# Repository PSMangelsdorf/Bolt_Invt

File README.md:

# Bolt_Invt
Open Source drop in logic board for Chevrolet Bolt inverter, based on the collective work of the Open Inverter Project, and especially that of Damien Maguire.

October 10, 2026 - Establishing repo for logic board development.  External pinout established from GM service information.  Internal pinout between logic and gate boards established via probing and tracing.

October 11, 2026 - Initial design completed by Claude - WARNING: This design is completely untested at this point.  ADDITIONAL WARNING: This design does not support the OEM Bolt drive motor/transmission at this time.  It does not drive the pump or read the IMS position.  It has not been configured with the Bolt resolver or temp sensors.

October 31, 2026 - A few updates made to the 5V regulation by Claude, also used Claude to produce gerbers and BOM.  First prototypes have been ordered.

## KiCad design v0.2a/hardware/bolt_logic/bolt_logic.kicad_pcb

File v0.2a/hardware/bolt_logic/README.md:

# bolt_logic — KiCad project

Replacement logic board for the Chevrolet Bolt EV traction inverter.

## Current state (v0.2a — redesign after the forum review)

- **Schematic v0.2a:** 7 hierarchical sheets, 245 parts, 162 nets, drawn as wired sheets in
  signal-flow order.
  - PDF: `../../docs/bolt_logic_schematic.pdf`
  - Design rationale: `../../docs/03-schematic-design.md`
  - What changed and why: `../../docs/06-forum-review.md`
- **PCB v0.2a:** 4 layers (signal / GND / power / signal), placed and routed. Prototype for
  review; see `../../docs/04-layout.md`.

## Regenerating

Everything is generated by scripts; edit the tables, not the outputs. You need KiCad 7+
(`pcbnew` Python module and `kicad-cli`). Routing also needs Java 21, `xvfb-run`,
FreeRouting 1.9 (`FREEROUTING_JAR`) and `shapely`.

```
python3 tools/gen_sch.py      # schematic sheets from tools/sch_design.py + sch_layout.py, netlist verified
python3 tools/gen_mech.py     # outline, holes, CN1/CN2 (asserts every pad position)
python3 tools/gen_layout.py   # netlist -> footprints, pad cross-check, placement
python3 tools/gen_route.py    # planes, buck / crystal / contactor copper, plane fan-out, FreeRouting, pours, DRC
python3 tools/gen_fab.py      # fab/: Gerbers + drill zip, JLCPCB BOM + CPL, full BOM, fab notes
```

`gen_route.py` takes about 10–15 minutes, most of it FreeRouting. Its working files go to
`route_work/` (not committed):
- `--import-only` re-imports the last routing run.
- `--stage2-only` keeps stage 1 and redoes only stage 2.

## Files

- `bolt_logic.kicad_pcb`: generated; don't hand-edit the mechanical items. Hand-tuning of
  the routing (see the review list) is expected later. Once that starts, stop re-running
  `gen_route.py`, because it would overwrite the hand edits.
- `tools/gen_mech.py`: single source of truth for mechanical dimensions.
- `tools/sch_design.py`: the schematic design table (every part, every pin → net).
- `tools/sch_layout.py`: where each symbol is drawn on its sheet, label directions, section notes.
- `tools/gen_layout.py`: placement regions (`GROUPS`), anchors, decoupling pairs (`NEAR`), the 10 mm CN1/CN2 clearance and the height check.
- `tools/gen_route.py`: net classes, In2 power-plane islands, routing flow, GND stitching, chassis ring.
- `tools/buck_block.py`: the hand-designed 5 V buck block (placement and copper).
- `tools/jlc_parts.py`, `tools/gen_fab.py`: proposed LCSC part per BOM line, and the fab package.
- `tools/gen_cn1_compare.py`: writes `../../docs/cn1_oem_vs_new.pdf`, the CN1 OEM-vs-new pin table.
  Re-run it after changing CN1 assignments in `sch_design.py`.
- `Bolt.pretty/`, `Bolt.kicad_sym`: project footprint and symbol libraries.

Coordinate frame and measurement provenance: `../../docs/02-mechanical.md`.
The project is saved in KiCad 7 format. It opens in KiCad 8/9, which will offer to upgrade
the file.

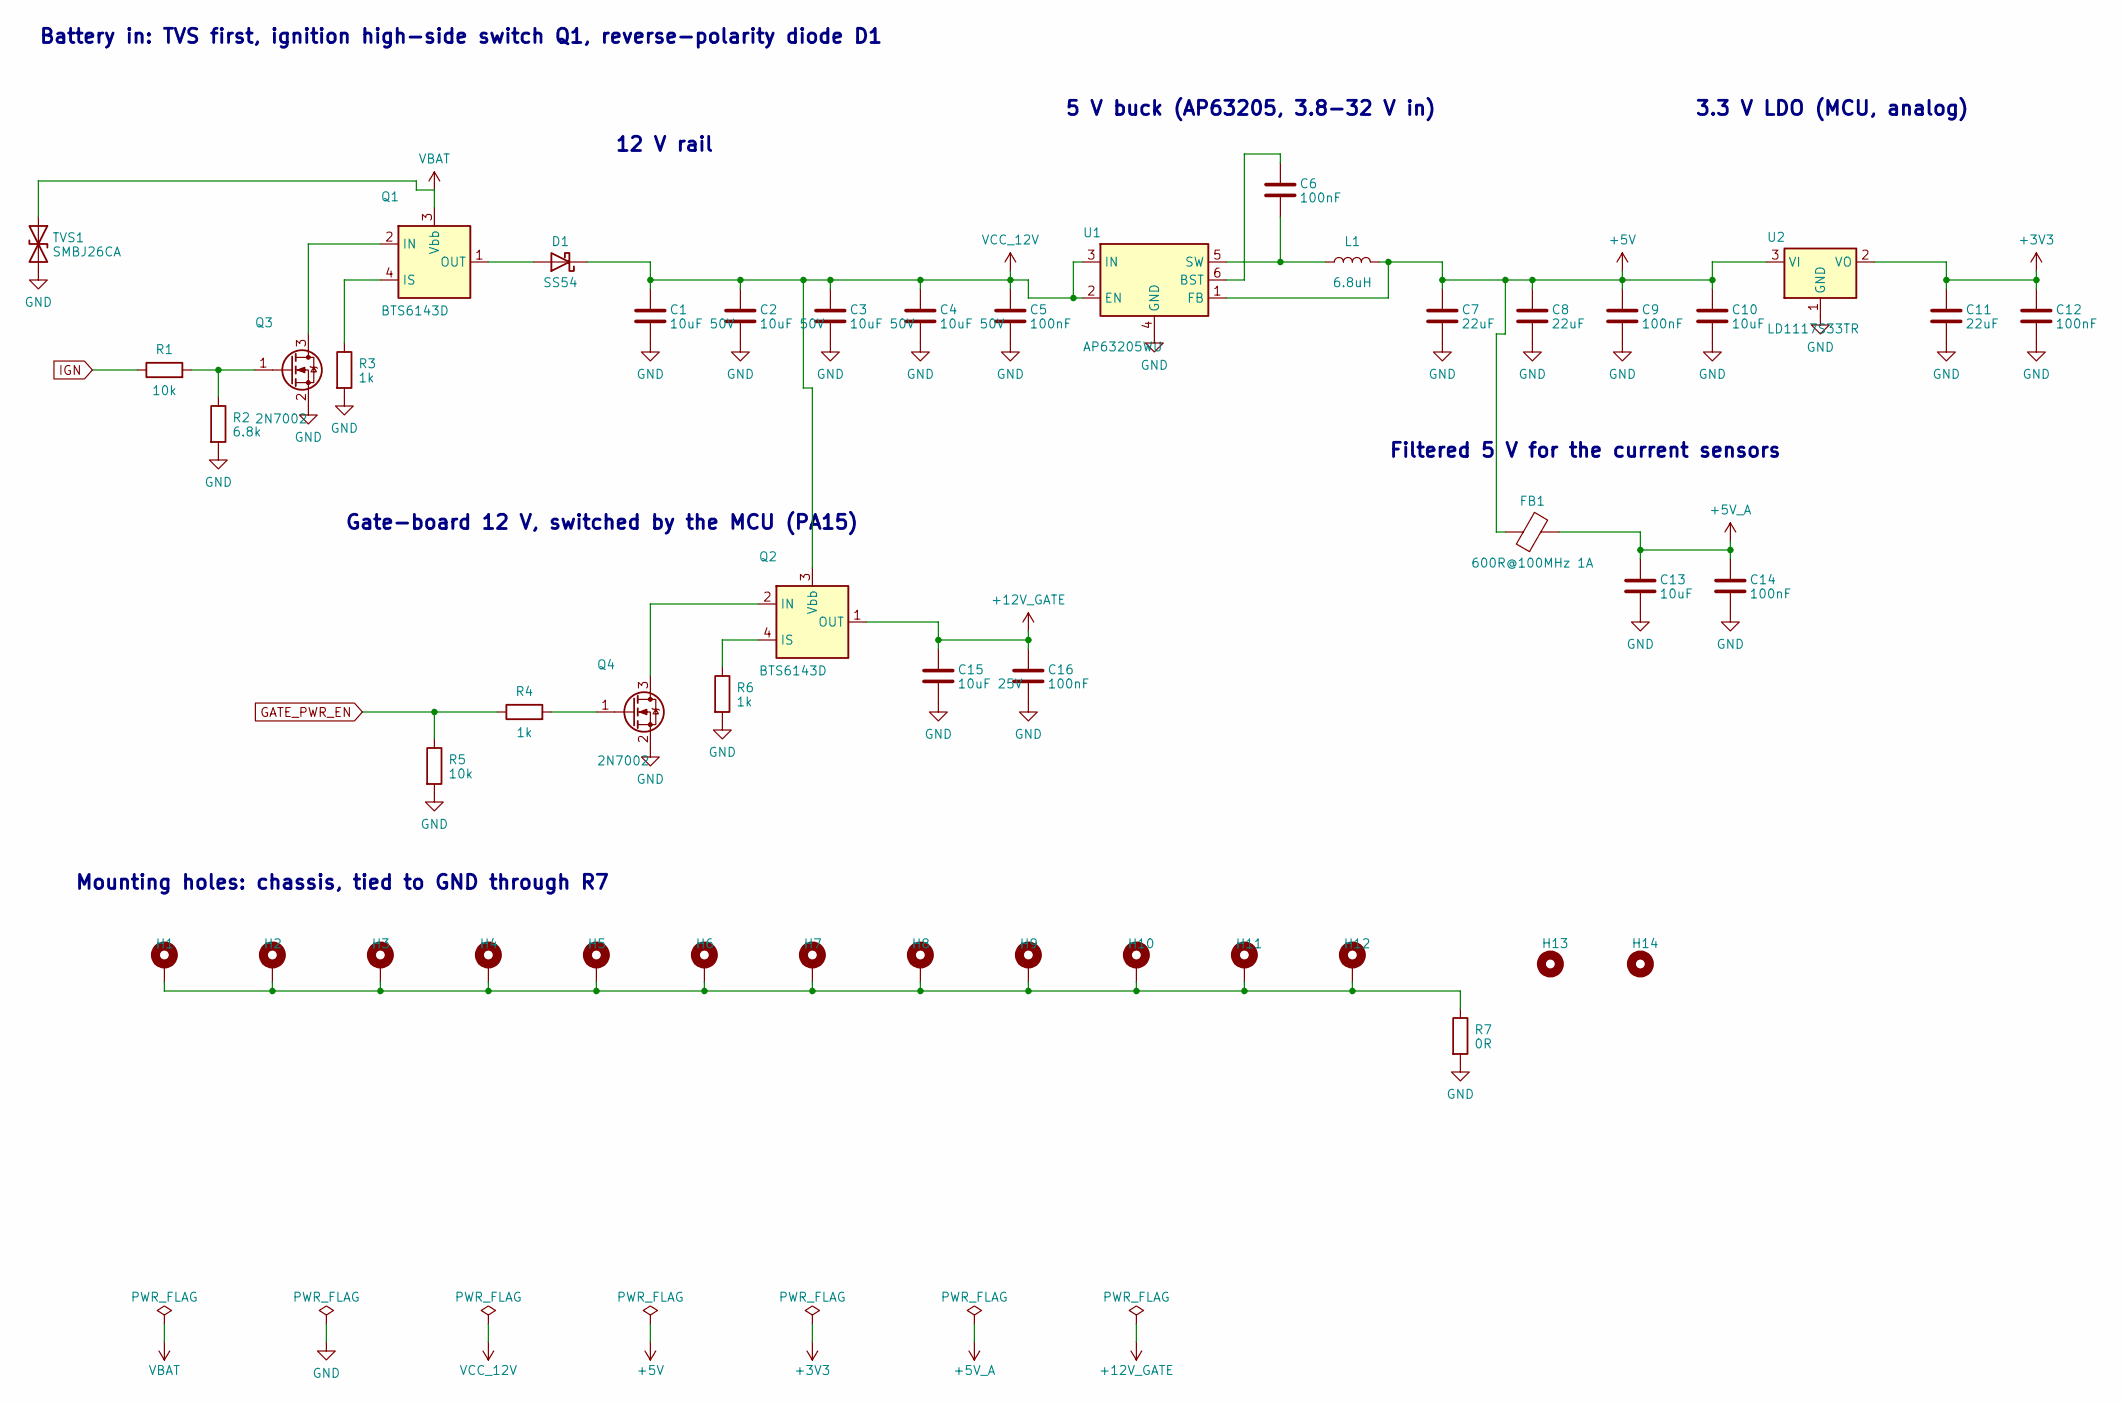
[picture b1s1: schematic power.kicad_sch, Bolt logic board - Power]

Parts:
C1, C2, C3, C4: 10uF 50V; C_1206_3216Metric
C5, C6, C9, C12, C14, C16: 100nF; C_0805_2012Metric
C7, C8, C11: 22uF; C_1206_3216Metric
C10, C13: 10uF; C_1206_3216Metric
C15: 10uF 25V; C_1206_3216Metric
D1: SS54; D_SMA
FB1: 600R@100MHz 1A; L_0805_2012Metric
H1, H2, H3, H4, H5, H6, H7, H8, H9, H10, H11, H12: MountingHole_4mm; MountingHole_4.0mm_Pad6.5
H13, H14: NPTH_4.5mm
L1: 6.8uH; L_Bourns_SRN6045TA
Q1, Q2: BTS6143D; TO-252-4
Q3, Q4: 2N7002; SOT-23
R1, R5: 10k; R_0805_2012Metric
R2: 6.8k; R_0805_2012Metric
R3, R4, R6: 1k; R_0805_2012Metric
R7: 0R; R_1206_3216Metric
TVS1: SMBJ26CA; D_SMB
U1: AP63205WU; TSOT-23-6
U2: LD1117S33TR; SOT-223-3_TabPin2

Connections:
+3V3: C11.1, C12.1, U2.2 (VO); also elsewhere on the board
+5V: C7.1, C8.1, C9.1, C10.1, FB1.1, L1.2, U1.1 (FB), U2.3 (VI); also elsewhere on the board
+5V_A: C13.1, C14.1, FB1.2; also elsewhere on the board
+12V_GATE: C15.1, C16.1, Q2.1 (OUT), Q2.5 (OUT); also elsewhere on the board
BST_5V: C6.1, U1.6 (BST)
CHASSIS: H1.1, H2.1, H3.1, H4.1, H5.1, H6.1, H7.1, H8.1, H9.1, H10.1, H11.1, H12.1, R7.1
GATE_PWR_EN: R4.1, R5.1; also elsewhere on the board
GND: C1.2, C2.2, C3.2, C4.2, C5.2, C7.2, C8.2, C9.2, C10.2, C11.2, C12.2, C13.2, C14.2, C15.2, C16.2, Q3.2 (S), Q4.2 (S), R2.2, R3.2, R5.2, R6.2, R7.2, TVS1.2 (A2), U1.4 (GND), U2.1 (GND); also elsewhere on the board
IGN: R1.1; also elsewhere on the board
Q1_G: Q3.1 (G), R1.2, R2.1
Q1_IN: Q1.2 (IN), Q3.3 (D)
Q1_IS: Q1.4 (IS), R3.1
Q2_G: Q4.1 (G), R4.2
Q2_IN: Q2.2 (IN), Q4.3 (D)
Q2_IS: Q2.4 (IS), R6.1
SW_5V: C6.2, L1.1, U1.5 (SW)
VBAT: Q1.3 (Vbb), TVS1.1 (A1); also elsewhere on the board
VBAT_SW: D1.2 (A), Q1.1 (OUT), Q1.5 (OUT)
VCC_12V: C1.1, C2.1, C3.1, C4.1, C5.1, D1.1 (K), Q2.3 (Vbb), U1.2 (EN), U1.3 (IN); also elsewhere on the board

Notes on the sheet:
Battery in: TVS first, ignition high-side switch Q1, reverse-polarity diode D1
12 V rail
5 V buck (AP63205, 3.8-32 V in)
3.3 V LDO (MCU, analog)
Gate-board 12 V, switched by the MCU (PA15)
Filtered 5 V for the current sensors
Mounting holes: chassis, tied to GND through R7

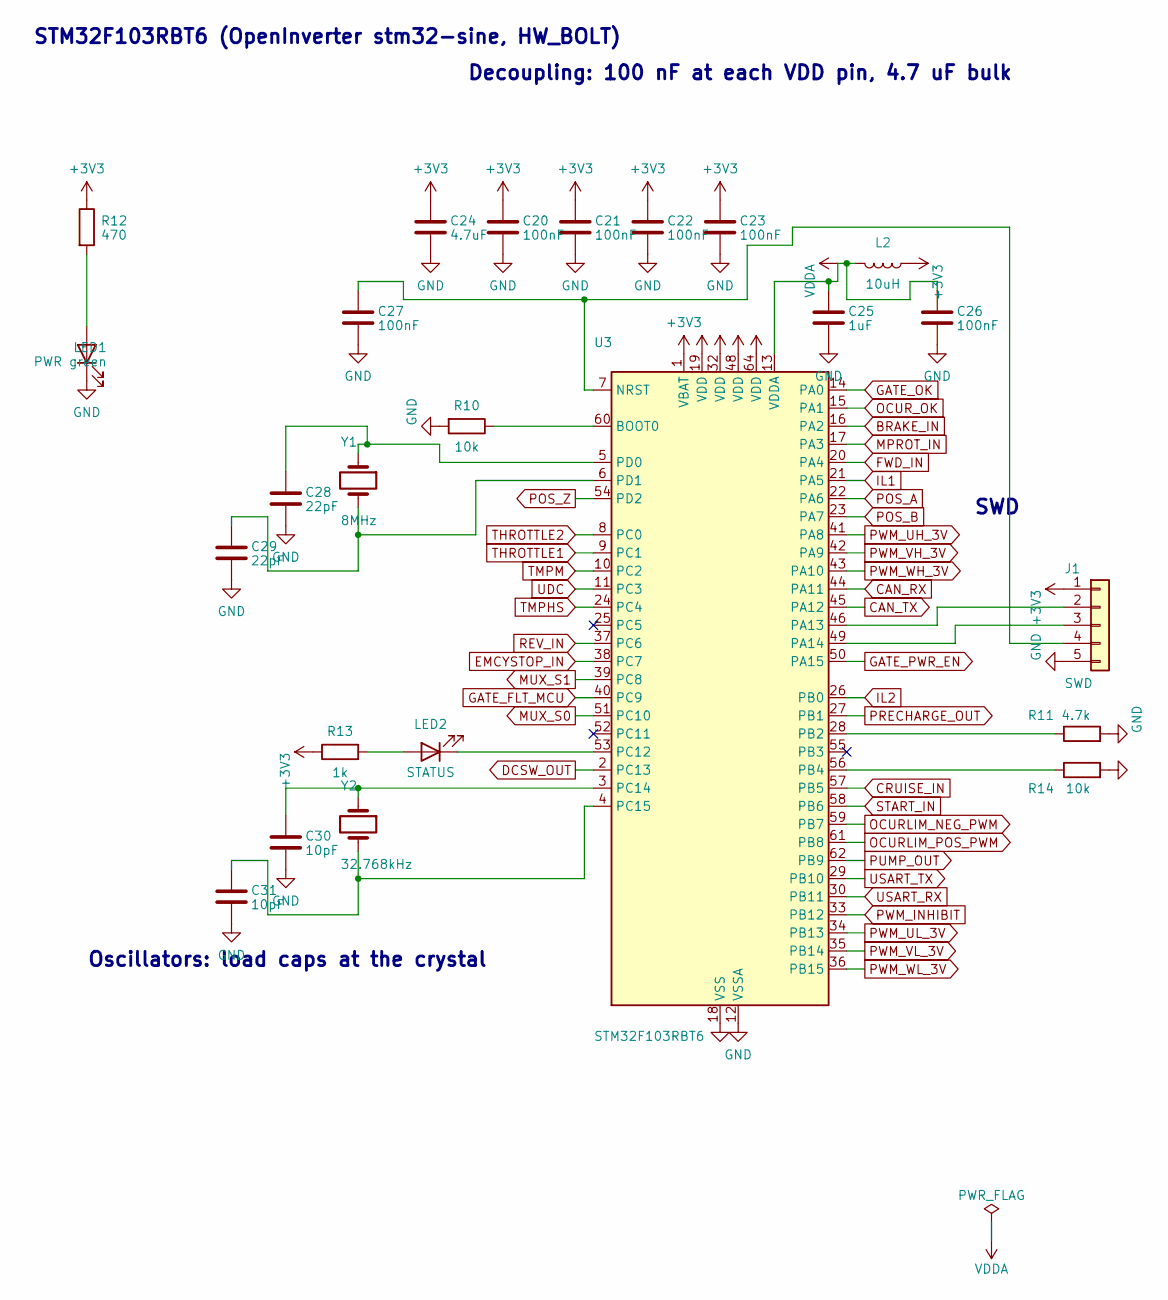
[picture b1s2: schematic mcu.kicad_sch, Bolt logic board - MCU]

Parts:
C20, C21, C22, C23, C26, C27: 100nF; C_0805_2012Metric
C24: 4.7uF; C_0805_2012Metric
C25: 1uF; C_0805_2012Metric
C28, C29: 22pF; C_0805_2012Metric
C30, C31: 10pF; C_0805_2012Metric
J1: SWD; PinHeader_1x05_P2.54mm_Vertical
L2: 10uH; L_0805_2012Metric
LED1: PWR green; LED_0805_2012Metric
LED2: STATUS; LED_0805_2012Metric
R10, R14: 10k; R_0805_2012Metric
R11: 4.7k; R_0805_2012Metric
R12: 470; R_0805_2012Metric
R13: 1k; R_0805_2012Metric
U3: STM32F103RBT6; LQFP-64_10x10mm_P0.5mm
Y1: 8MHz; Crystal_SMD_5032-2Pin_5.0x3.2mm
Y2: 32.768kHz; Crystal_SMD_3215-2Pin_3.2x1.5mm

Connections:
+3V3: C20.1, C21.1, C22.1, C23.1, C24.1, J1.1, L2.1, R12.1, R13.1, U3.1 (VBAT), U3.19 (VDD), U3.32 (VDD), U3.48 (VDD), U3.64 (VDD); also elsewhere on the board
BOARD_ID: R14.1, U3.56 (PB4)
BOOT0: R10.1, U3.60 (BOOT0)
BOOT1: R11.1, U3.28 (PB2)
BRAKE_IN: U3.16 (PA2); also elsewhere on the board
CAN_RX: U3.44 (PA11); also elsewhere on the board
CAN_TX: U3.45 (PA12); also elsewhere on the board
CRUISE_IN: U3.57 (PB5); also elsewhere on the board
DCSW_OUT: U3.2 (PC13); also elsewhere on the board
EMCYSTOP_IN: U3.38 (PC7); also elsewhere on the board
FWD_IN: U3.20 (PA4); also elsewhere on the board
GATE_FLT_MCU: U3.40 (PC9); also elsewhere on the board
GATE_OK: U3.14 (PA0); also elsewhere on the board
GATE_PWR_EN: U3.50 (PA15); also elsewhere on the board
GND: C20.2, C21.2, C22.2, C23.2, C24.2, C25.2, C26.2, C27.2, C28.2, C29.2, C30.2, C31.2, J1.5, LED1.1 (K), R10.2, R11.2, R14.2, U3.12 (VSSA), U3.18 (VSS), U3.31 (VSS), U3.47 (VSS), U3.63 (VSS); also elsewhere on the board
IL1: U3.21 (PA5); also elsewhere on the board
IL2: U3.26 (PB0); also elsewhere on the board
LED1_A: LED1.2 (A), R12.2
LED2_A: LED2.2 (A), R13.2
LED_OUT: LED2.1 (K), U3.53 (PC12)
MPROT_IN: U3.17 (PA3); also elsewhere on the board
MUX_S0: U3.51 (PC10); also elsewhere on the board
MUX_S1: U3.39 (PC8); also elsewhere on the board
NRST: C27.1, J1.4, U3.7 (NRST)
OCURLIM_NEG_PWM: U3.59 (PB7); also elsewhere on the board
OCURLIM_POS_PWM: U3.61 (PB8); also elsewhere on the board
OCUR_OK: U3.15 (PA1); also elsewhere on the board
OSC32_IN: C30.1, U3.3 (PC14), Y2.1
OSC32_OUT: C31.1, U3.4 (PC15), Y2.2
OSC_IN: C28.1, U3.5 (PD0), Y1.1
OSC_OUT: C29.1, U3.6 (PD1), Y1.2
POS_A: U3.22 (PA6); also elsewhere on the board
POS_B: U3.23 (PA7); also elsewhere on the board
POS_Z: U3.54 (PD2); also elsewhere on the board
PRECHARGE_OUT: U3.27 (PB1); also elsewhere on the board
PUMP_OUT: U3.62 (PB9); also elsewhere on the board
PWM_INHIBIT: U3.33 (PB12); also elsewhere on the board
PWM_UH_3V: U3.41 (PA8); also elsewhere on the board
PWM_UL_3V: U3.34 (PB13); also elsewhere on the board
PWM_VH_3V: U3.42 (PA9); also elsewhere on the board
PWM_VL_3V: U3.35 (PB14); also elsewhere on the board
PWM_WH_3V: U3.43 (PA10); also elsewhere on the board
PWM_WL_3V: U3.36 (PB15); also elsewhere on the board
REV_IN: U3.37 (PC6); also elsewhere on the board
START_IN: U3.58 (PB6); also elsewhere on the board
SWCLK: J1.3, U3.49 (PA14)
SWDIO: J1.2, U3.46 (PA13)
THROTTLE1: U3.9 (PC1); also elsewhere on the board
THROTTLE2: U3.8 (PC0); also elsewhere on the board
TMPHS: U3.24 (PC4); also elsewhere on the board
TMPM: U3.10 (PC2); also elsewhere on the board
UDC: U3.11 (PC3); also elsewhere on the board
USART_RX: U3.30 (PB11); also elsewhere on the board
USART_TX: U3.29 (PB10); also elsewhere on the board
VDDA: C25.1, C26.1, L2.2, U3.13 (VDDA)

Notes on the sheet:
STM32F103RBT6 (OpenInverter stm32-sine, HW_BOLT)
Decoupling: 100 nF at each VDD pin, 4.7 uF bulk
Oscillators: load caps at the crystal
SWD

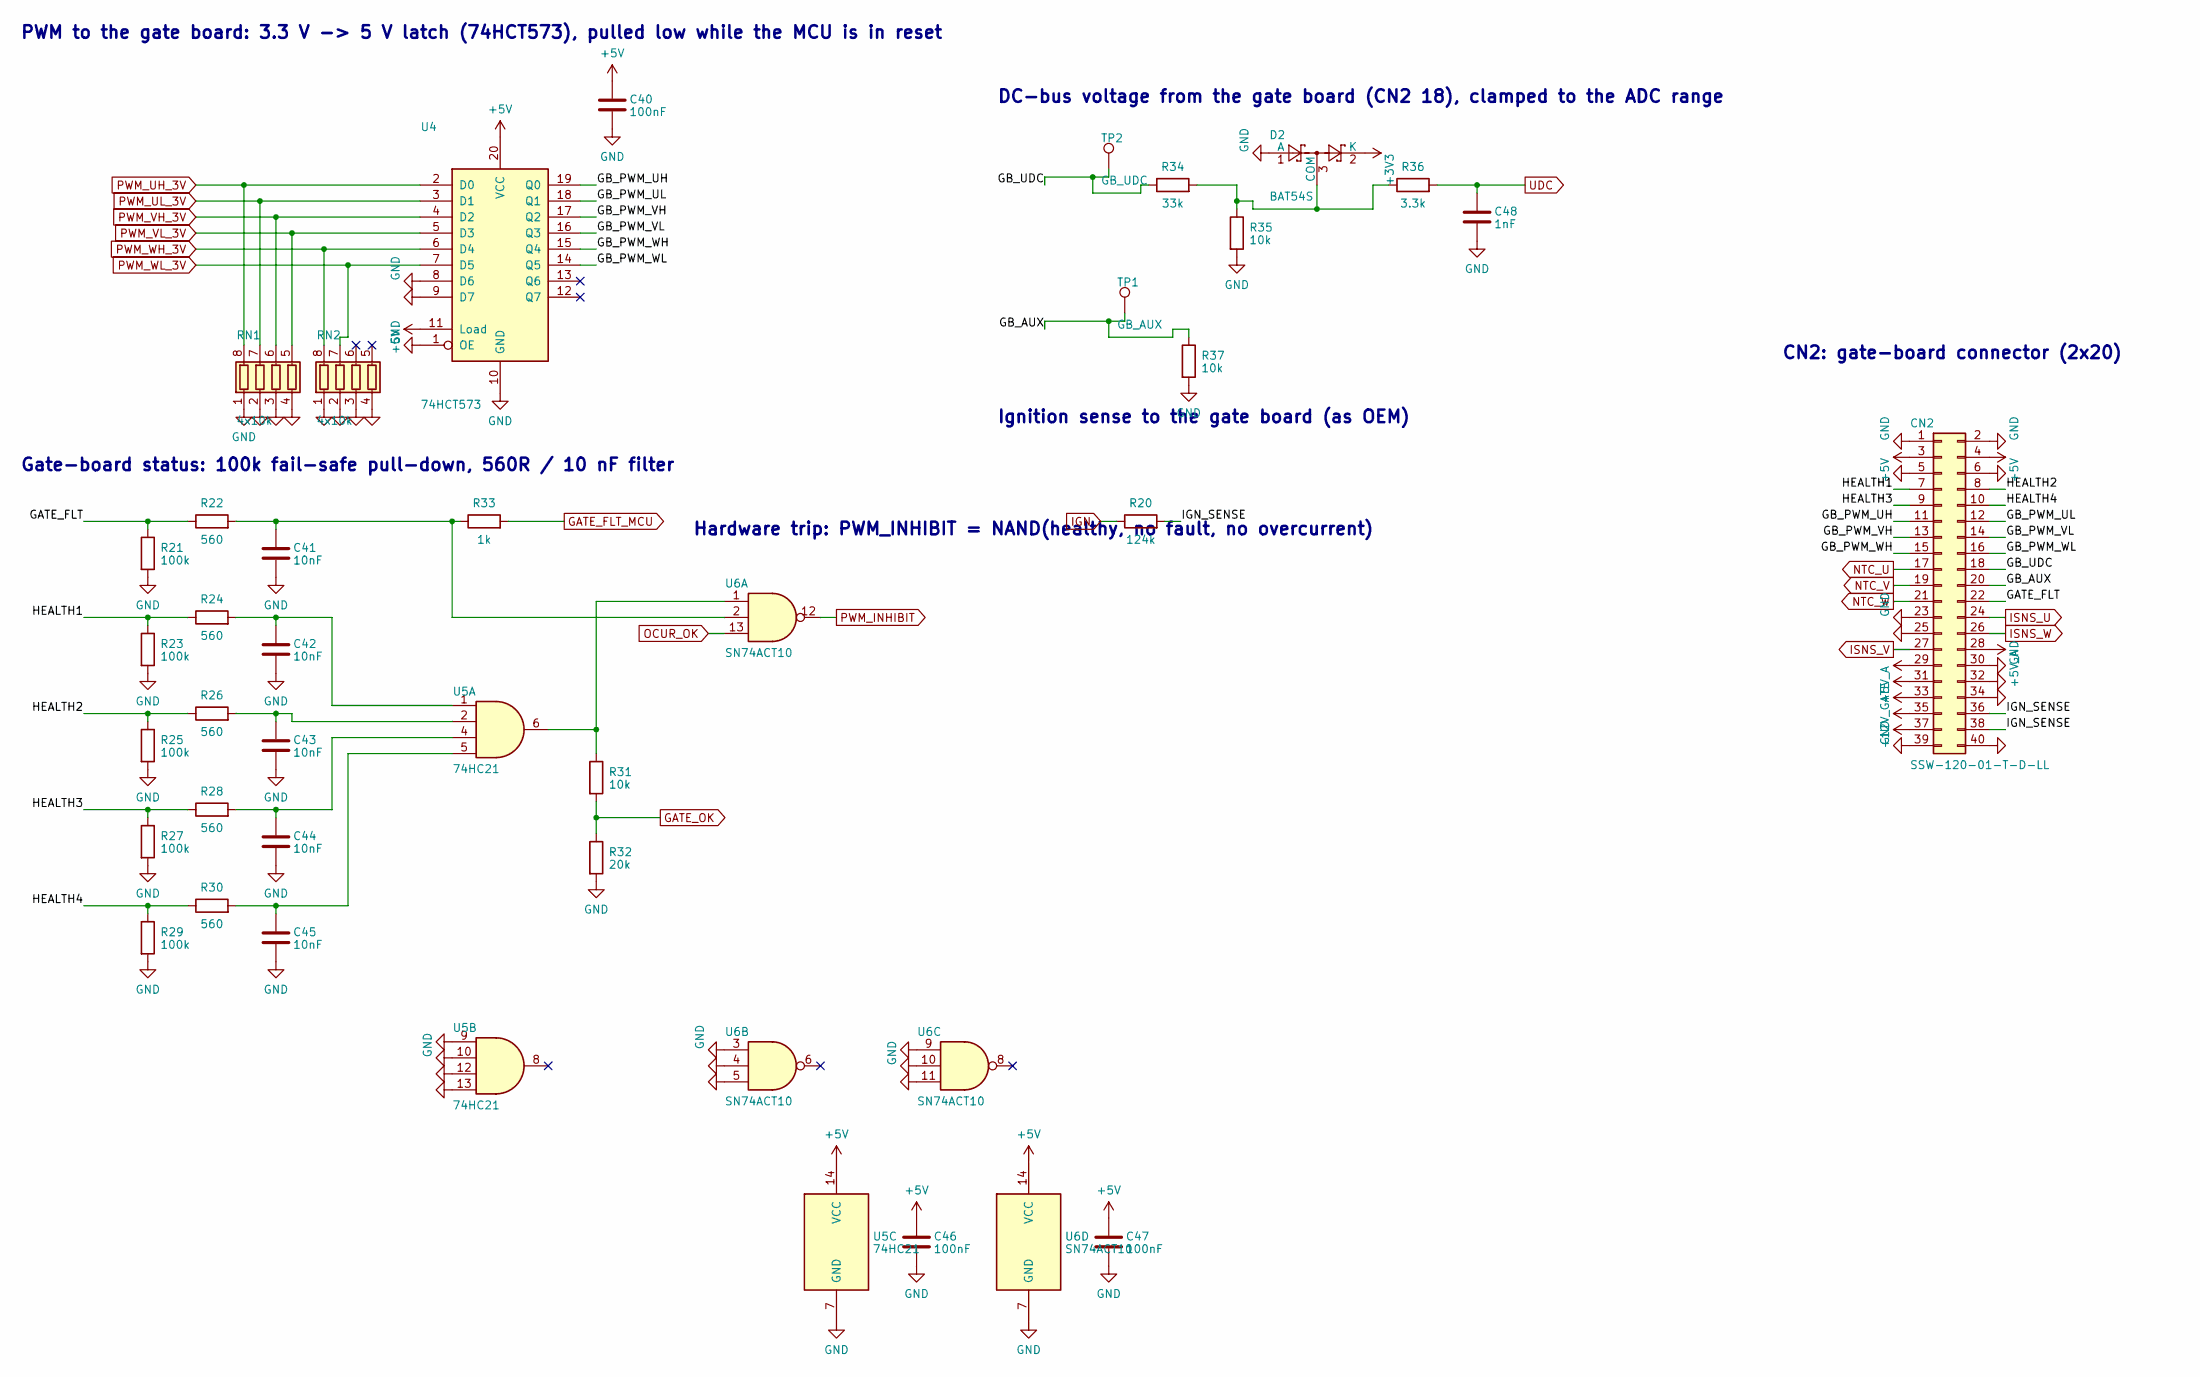
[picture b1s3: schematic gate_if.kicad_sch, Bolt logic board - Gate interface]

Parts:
C40, C46, C47: 100nF; C_0805_2012Metric
C41, C42, C43, C44, C45: 10nF; C_0805_2012Metric
C48: 1nF; C_0805_2012Metric
CN2: SSW-120-01-T-D-LL; CN2_2x20_P2.54_Receptacle_Back
D2: BAT54S; SOT-23
R20: 124k; R_0805_2012Metric
R21, R23, R25, R27, R29: 100k; R_0805_2012Metric
R22, R24, R26, R28, R30: 560; R_0805_2012Metric
R31, R35, R37: 10k; R_0805_2012Metric
R32: 20k; R_0805_2012Metric
R33: 1k; R_0805_2012Metric
R34: 33k; R_0805_2012Metric
R36: 3.3k; R_0805_2012Metric
RN1, RN2: 4x10k; R_Array_Convex_4x0603
TP1: GB_AUX; TestPoint_Pad_D1.5mm
TP2: GB_UDC; TestPoint_Pad_D1.5mm
U4: 74HCT573; SOIC-20W_7.5x12.8mm_P1.27mm
U5: 74HC21; SOIC-14_3.9x8.7mm_P1.27mm
U6: SN74ACT10; SOIC-14_3.9x8.7mm_P1.27mm

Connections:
+3V3: D2.2 (K); also elsewhere on the board
+5V: C40.1, C46.1, C47.1, CN2.3, CN2.4, U4.11 (Load), U4.20 (VCC), U5.14 (VCC), U6.14 (VCC); also elsewhere on the board
+5V_A: CN2.28, CN2.29; also elsewhere on the board
+12V_GATE: CN2.31, CN2.33, CN2.35, CN2.37; also elsewhere on the board
GATE_FLT: CN2.22, R21.1, R22.1
GATE_FLT_F: C41.1, R22.2, R33.1, U6.2
GATE_FLT_MCU: R33.2; also elsewhere on the board
GATE_OK: R31.2, R32.1; also elsewhere on the board
GATE_OK_5V: R31.1, U5.6, U6.1
GB_AUX: CN2.20, R37.1, TP1.1
GB_PWM_UH: CN2.11, U4.19 (Q0)
GB_PWM_UL: CN2.12, U4.18 (Q1)
GB_PWM_VH: CN2.13, U4.17 (Q2)
GB_PWM_VL: CN2.14, U4.16 (Q3)
GB_PWM_WH: CN2.15, U4.15 (Q4)
GB_PWM_WL: CN2.16, U4.14 (Q5)
GB_UDC: CN2.18, R34.1, TP2.1
GND: C40.2, C41.2, C42.2, C43.2, C44.2, C45.2, C46.2, C47.2, C48.2, CN2.1, CN2.2, CN2.5, CN2.6, CN2.23, CN2.25, CN2.30, CN2.32, CN2.34, CN2.39, CN2.40, D2.1 (A), R21.2, R23.2, R25.2, R27.2, R29.2, R32.2, R35.2, R37.2, RN1.1 (R1.1), RN1.2 (R2.1), RN1.3 (R3.1), RN1.4 (R4.1), RN2.1 (R1.1), RN2.2 (R2.1), RN2.3 (R3.1), RN2.4 (R4.1), U4.1 (OE), U4.8 (D6), U4.9 (D7), U4.10 (GND), U5.7 (GND), U5.9, U5.10, U5.12, U5.13, U6.3, U6.4, U6.5, U6.7 (GND), U6.9, U6.10, U6.11; also elsewhere on the board
HEALTH1: CN2.7, R23.1, R24.1
HEALTH1_F: C42.1, R24.2, U5.1
HEALTH2: CN2.8, R25.1, R26.1
HEALTH2_F: C43.1, R26.2, U5.2
HEALTH3: CN2.9, R27.1, R28.1
HEALTH3_F: C44.1, R28.2, U5.4
HEALTH4: CN2.10, R29.1, R30.1
HEALTH4_F: C45.1, R30.2, U5.5
IGN: R20.1; also elsewhere on the board
IGN_SENSE: CN2.36, CN2.38, R20.2
ISNS_U: CN2.24; also elsewhere on the board
ISNS_V: CN2.27; also elsewhere on the board
ISNS_W: CN2.26; also elsewhere on the board
NTC_U: CN2.17; also elsewhere on the board
NTC_V: CN2.19; also elsewhere on the board
NTC_W: CN2.21; also elsewhere on the board
OCUR_OK: U6.13; also elsewhere on the board
PWM_INHIBIT: U6.12; also elsewhere on the board
PWM_UH_3V: RN1.8 (R1.2), U4.2 (D0); also elsewhere on the board
PWM_UL_3V: RN1.7 (R2.2), U4.3 (D1); also elsewhere on the board
PWM_VH_3V: RN1.6 (R3.2), U4.4 (D2); also elsewhere on the board
PWM_VL_3V: RN1.5 (R4.2), U4.5 (D3); also elsewhere on the board
PWM_WH_3V: RN2.8 (R1.2), U4.6 (D4); also elsewhere on the board
PWM_WL_3V: RN2.7 (R2.2), U4.7 (D5); also elsewhere on the board
UDC: C48.1, R36.2; also elsewhere on the board
UDC_DIV: D2.3 (COM), R34.2, R35.1, R36.1

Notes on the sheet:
PWM to the gate board: 3.3 V -> 5 V latch (74HCT573), pulled low while the MCU is in reset
Gate-board status: 100k fail-safe pull-down, 560R / 10 nF filter
Hardware trip: PWM_INHIBIT = NAND(healthy, no fault, no overcurrent)
DC-bus voltage from the gate board (CN2 18), clamped to the ADC range
Ignition sense to the gate board (as OEM)
CN2: gate-board connector (2x20)

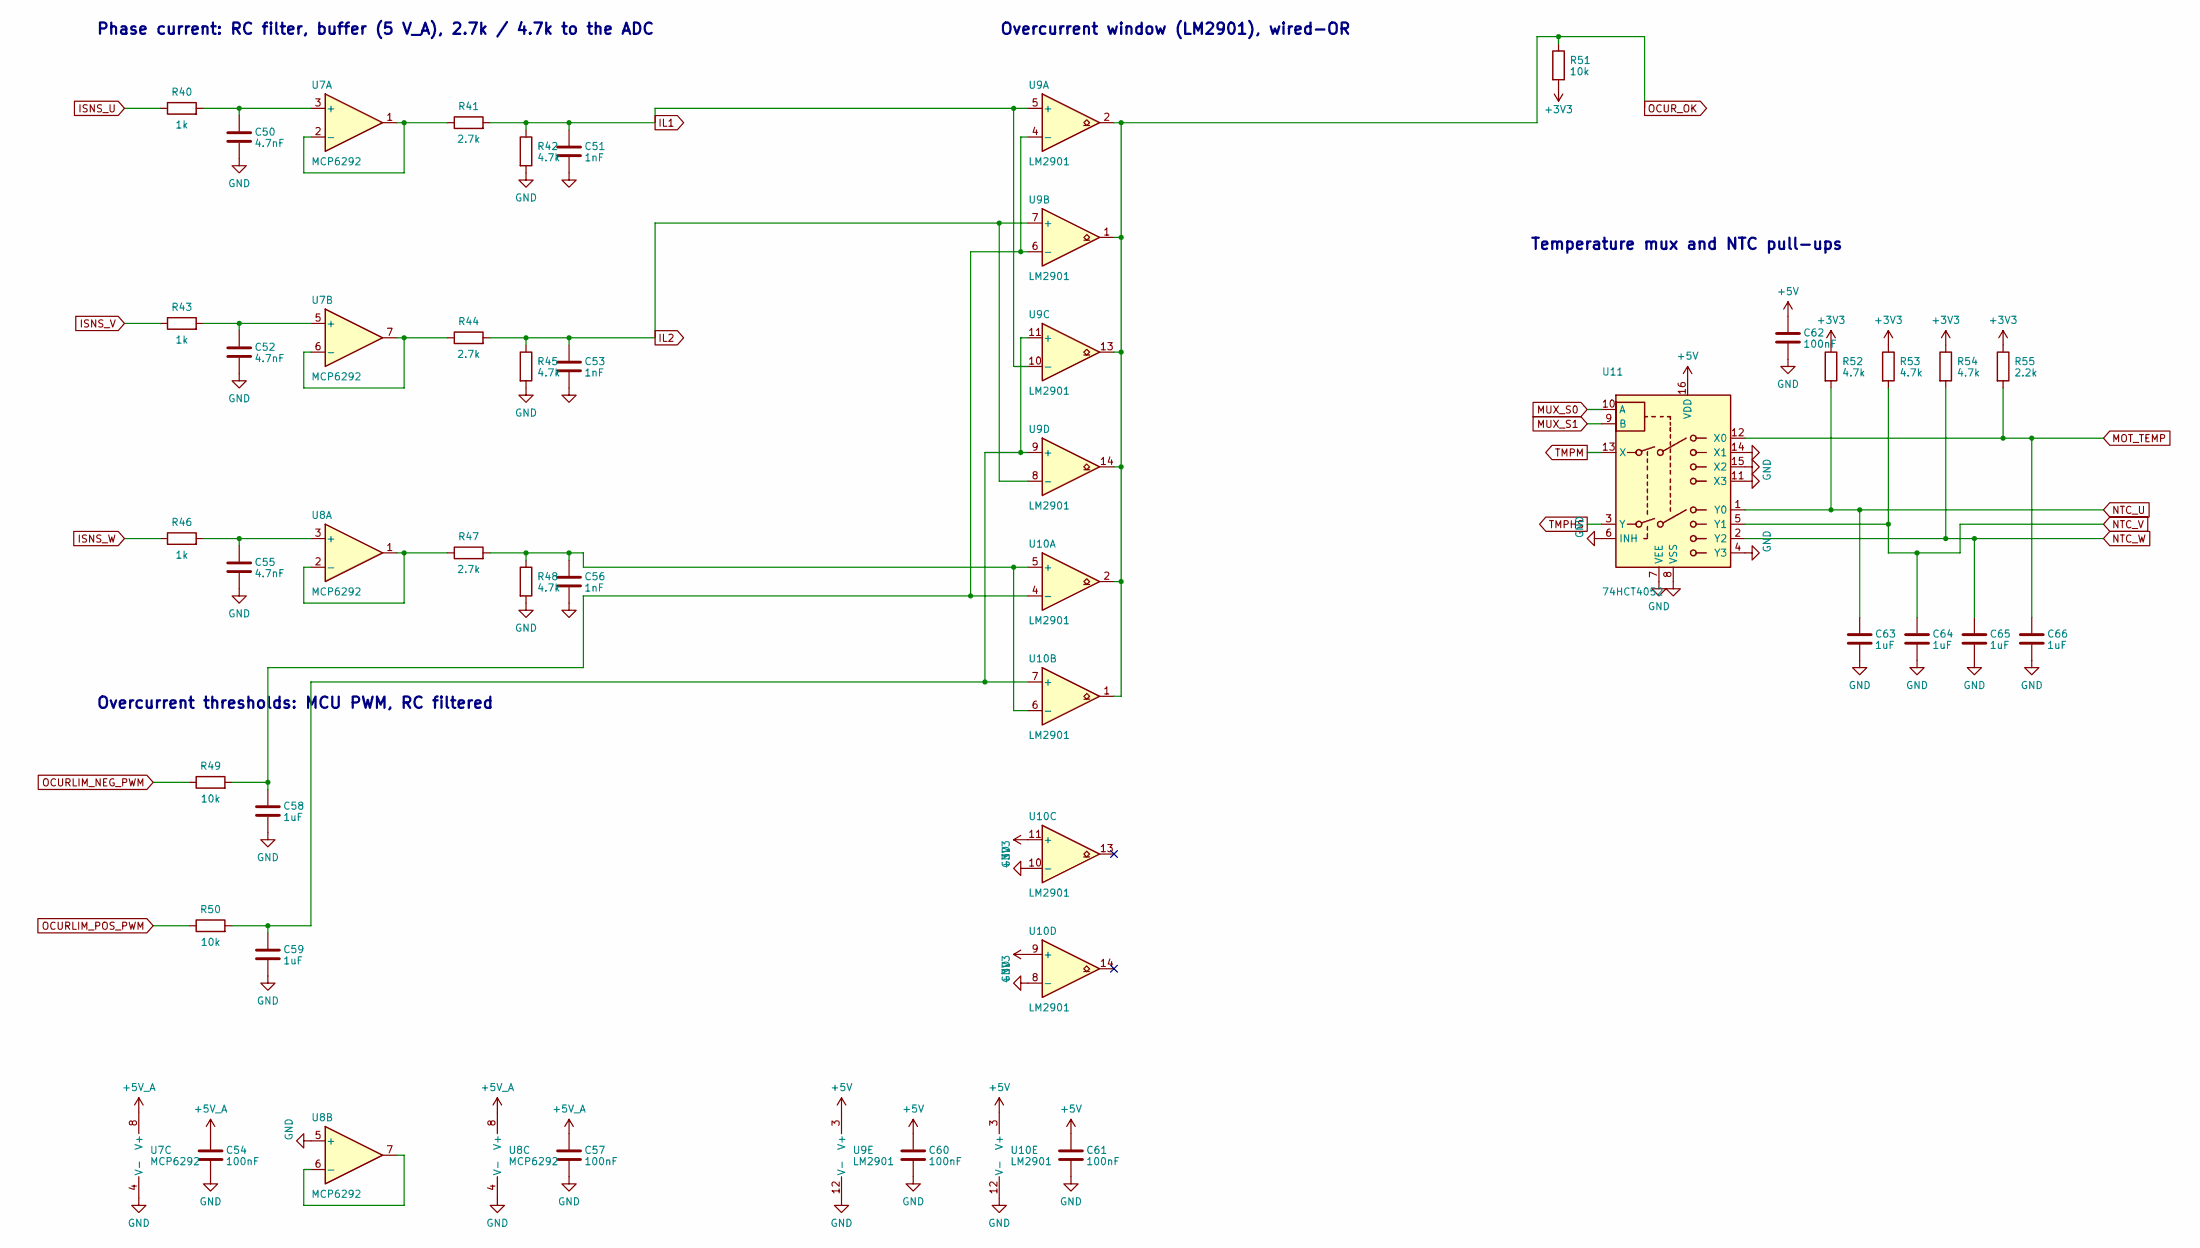
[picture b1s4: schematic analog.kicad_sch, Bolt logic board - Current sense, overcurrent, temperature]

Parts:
C50, C52, C55: 4.7nF; C_0805_2012Metric
C51, C53, C56: 1nF; C_0805_2012Metric
C54, C57, C60, C61, C62: 100nF; C_0805_2012Metric
C58, C59, C63, C64, C65, C66: 1uF; C_0805_2012Metric
R40, R43, R46: 1k; R_0805_2012Metric
R41, R44, R47: 2.7k; R_0805_2012Metric
R42, R45, R48, R52, R53, R54: 4.7k; R_0805_2012Metric
R49, R50, R51: 10k; R_0805_2012Metric
R55: 2.2k; R_0805_2012Metric
U7, U8: MCP6292; SOIC-8_3.9x4.9mm_P1.27mm
U9, U10: LM2901; SOIC-14_3.9x8.7mm_P1.27mm
U11: 74HCT4052; SOIC-16_3.9x9.9mm_P1.27mm

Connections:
+3V3: R51.2, R52.1, R53.1, R54.1, R55.1, U10.9 (+), U10.11 (+); also elsewhere on the board
+5V: C60.1, C61.1, C62.1, U9.3 (V+), U10.3 (V+), U11.16 (VDD); also elsewhere on the board
+5V_A: C54.1, C57.1, U7.8 (V+), U8.8 (V+); also elsewhere on the board
GND: C50.2, C51.2, C52.2, C53.2, C54.2, C55.2, C56.2, C57.2, C58.2, C59.2, C60.2, C61.2, C62.2, C63.2, C64.2, C65.2, C66.2, R42.2, R45.2, R48.2, U7.4 (V-), U8.4 (V-), U8.5 (+), U9.12 (V-), U10.8 (-), U10.10 (-), U10.12 (V-), U11.4 (Y3), U11.6 (INH), U11.7 (VEE), U11.8 (VSS), U11.11 (X3), U11.14 (X1), U11.15 (X2); also elsewhere on the board
IL1: C51.1, R41.2, R42.1, U9.5 (+), U9.10 (-); also elsewhere on the board
IL2: C53.1, R44.2, R45.1, U9.7 (+), U9.8 (-); also elsewhere on the board
ISNS_U: R40.1; also elsewhere on the board
ISNS_U_BUF: R41.1, U7.1, U7.2 (-)
ISNS_U_F: C50.1, R40.2, U7.3 (+)
ISNS_V: R43.1; also elsewhere on the board
ISNS_V_BUF: R44.1, U7.6 (-), U7.7
ISNS_V_F: C52.1, R43.2, U7.5 (+)
ISNS_W: R46.1; also elsewhere on the board
ISNS_W_BUF: R47.1, U8.1, U8.2 (-)
ISNS_W_F: C55.1, R46.2, U8.3 (+)
IW_S: C56.1, R47.2, R48.1, U10.5 (+), U10.6 (-)
MOT_TEMP: C66.1, R55.2, U11.12 (X0); also elsewhere on the board
MUX_S0: U11.10 (A); also elsewhere on the board
MUX_S1: U11.9 (B); also elsewhere on the board
NTC_U: C63.1, R52.2, U11.1 (Y0); also elsewhere on the board
NTC_V: C64.1, R53.2, U11.5 (Y1); also elsewhere on the board
NTC_W: C65.1, R54.2, U11.2 (Y2); also elsewhere on the board
OCURLIM_NEG_PWM: R49.1; also elsewhere on the board
OCURLIM_POS_PWM: R50.1; also elsewhere on the board
OCUR_NEG: C58.1, R49.2, U9.4 (-), U9.6 (-), U10.4 (-)
OCUR_OK: R51.1, U9.1, U9.2, U9.13, U9.14, U10.1, U10.2; also elsewhere on the board
OCUR_POS: C59.1, R50.2, U9.9 (+), U9.11 (+), U10.7 (+)
TMPHS: U11.3 (Y); also elsewhere on the board
TMPM: U11.13 (X); also elsewhere on the board
U8B_OUT: U8.6 (-), U8.7

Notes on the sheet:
Phase current: RC filter, buffer (5 V_A), 2.7k / 4.7k to the ADC
Overcurrent thresholds: MCU PWM, RC filtered
Overcurrent window (LM2901), wired-OR
Temperature mux and NTC pull-ups

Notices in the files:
v0.2a/hardware/bolt_logic/bolt_logic.kicad_pcb:
COPYRIGHT 2026
